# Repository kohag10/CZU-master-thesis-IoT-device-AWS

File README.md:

# CZU-master-thesis-IoT-device-AWS

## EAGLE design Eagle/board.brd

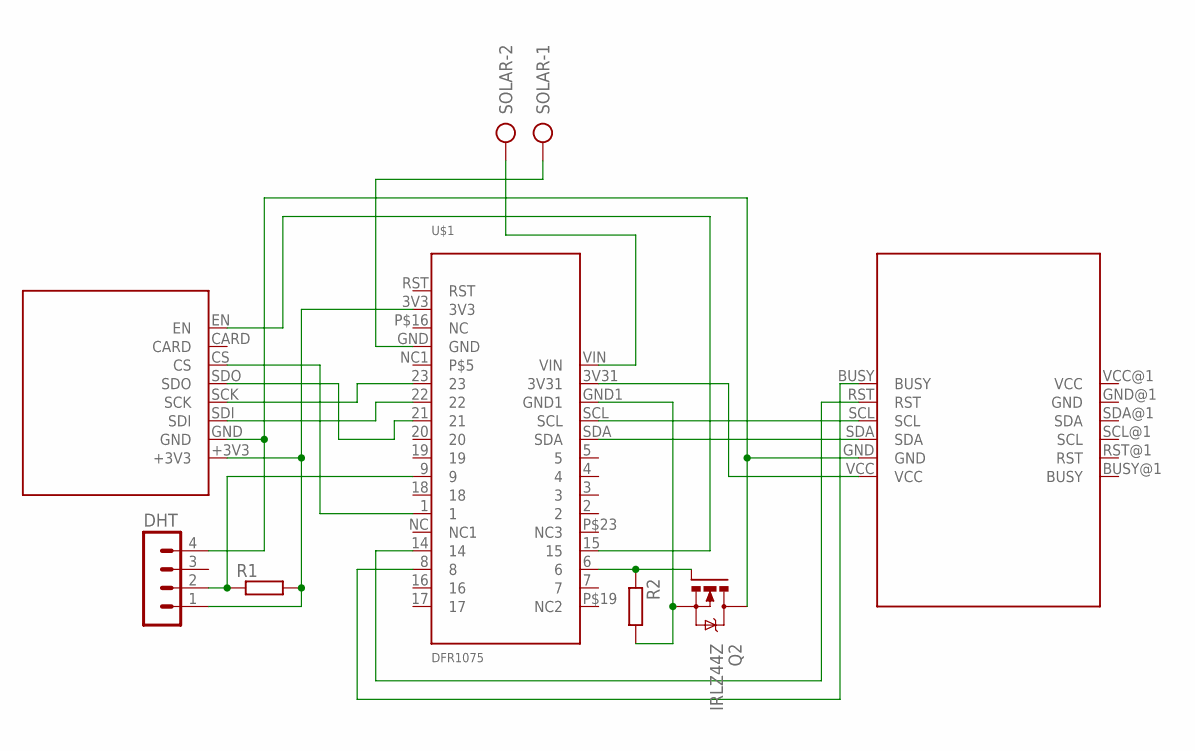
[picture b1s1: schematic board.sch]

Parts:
DHT: MA04-1
Q2: IRLZ44Z; TO220BH
R1, R2: R0207/10; 0207/10
SOLAR: AK300/2
U$1: DFR1075
U$2: 1.9INCH_WAVESHARE_E-PAPER
U$3: LASKAKIT-MICROSD-READER

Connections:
BUSY: U$1.8, U$2.BUSY
GND: DHT.4, Q2.D, U$2.GND, U$3.GND
unnamed: Q2.G, R2.1, U$1.6
unnamed: Q2.S, R2.2, U$1.GND1
unnamed: U$1.SCL, U$2.SCL
unnamed: U$1.SDA, U$2.SDA
unnamed: U$1.3V31, U$2.VCC
unnamed: SOLAR.2, U$1.VIN
unnamed: DHT.1, R1.2, U$1.3V3, U$3.+3V3
unnamed: DHT.2, R1.1, U$1.9
unnamed: U$1.22, U$3.SDI
unnamed: U$1.23, U$3.SCK
unnamed: U$1.21, U$3.SDO
unnamed: U$1.1, U$3.CS
unnamed: SOLAR.1, U$1.GND
unnamed: U$1.15, U$3.EN
RST: U$1.14, U$2.RST

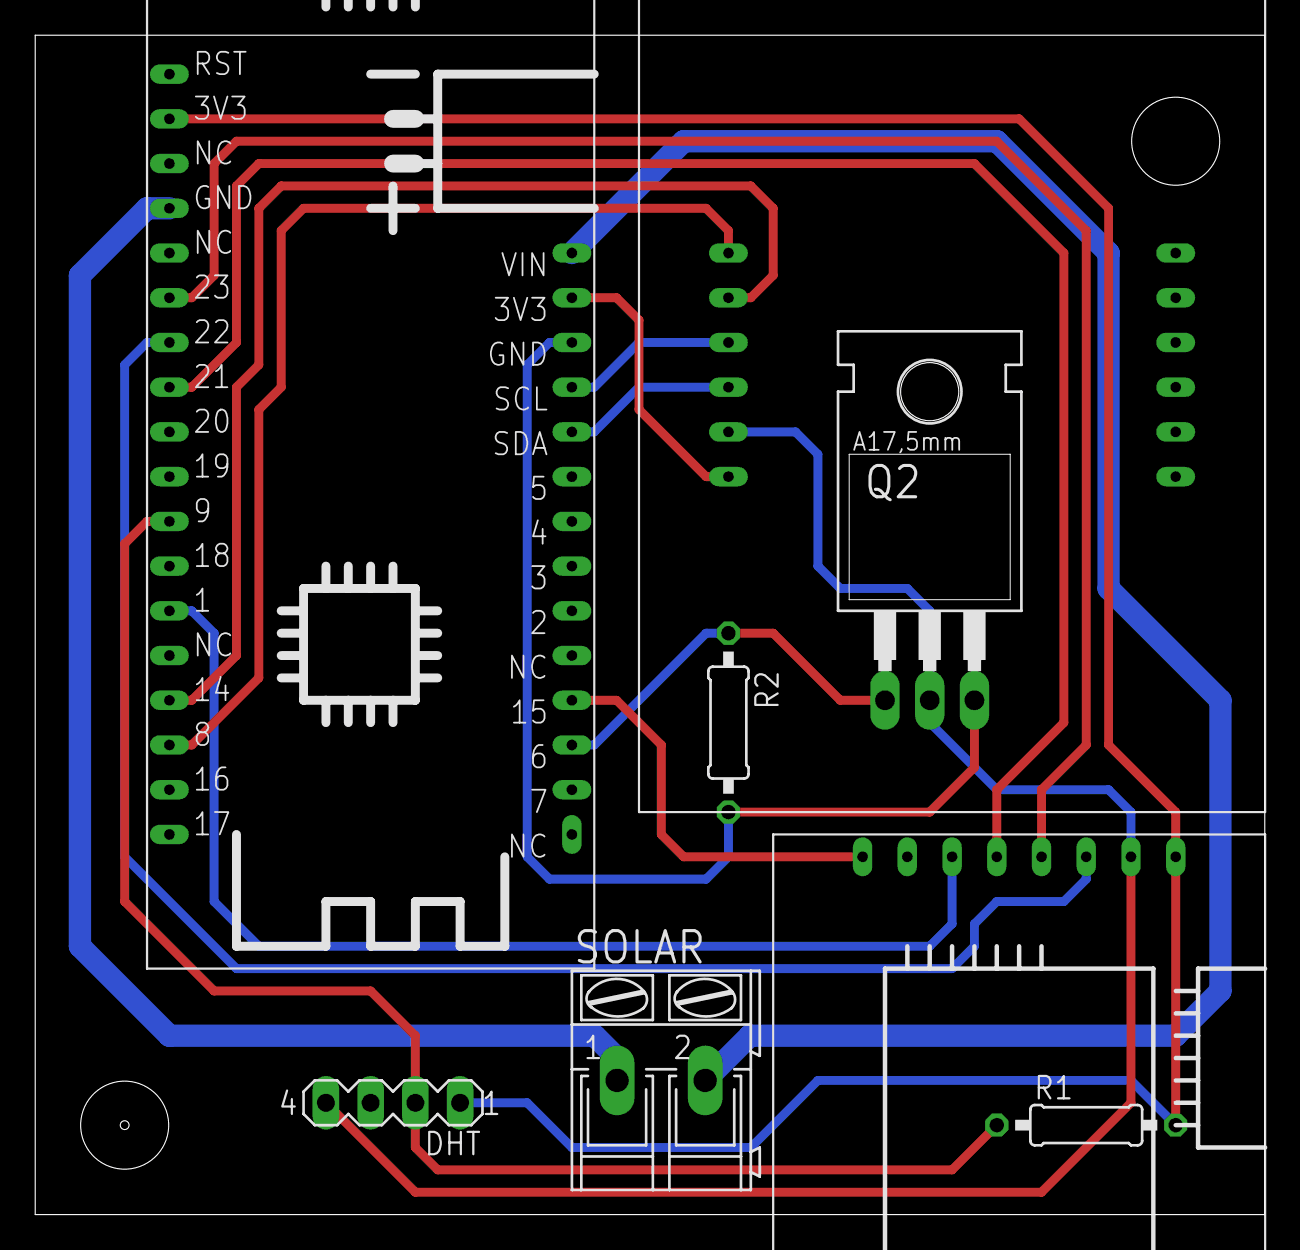
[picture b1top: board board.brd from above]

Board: 2 copper layers, 69.8 x 67.0 mm, 8 parts (0 on the bottom side), 17 nets.

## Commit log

2026-04-17 Create Arduino file
